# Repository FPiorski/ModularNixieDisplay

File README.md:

# Modular PCB for Z5730M Nixie tubes
#### Because ten small boards are better than a single big one
Schematics and board desing done in KiCad
##### ~~TODO for Rev 2:~~
* ~~Fix Z5730M footprint~~
  * ~~Widen mounting holes to account for desoldered tubes~~
  * ~~Bring mounting holes closer to center~~
* ~~Fix transistor pinout~~
  * ~~Change from Q_NPN_CBE to Q_NPN_BEC on the schematic~~
* ~~Reannotate components on the schematic~~
  * ~~Make R_n connect to Q_n and drive digit n~~
* ~~Add Rev 2 markings, of course~~

##### Revision 2 done!

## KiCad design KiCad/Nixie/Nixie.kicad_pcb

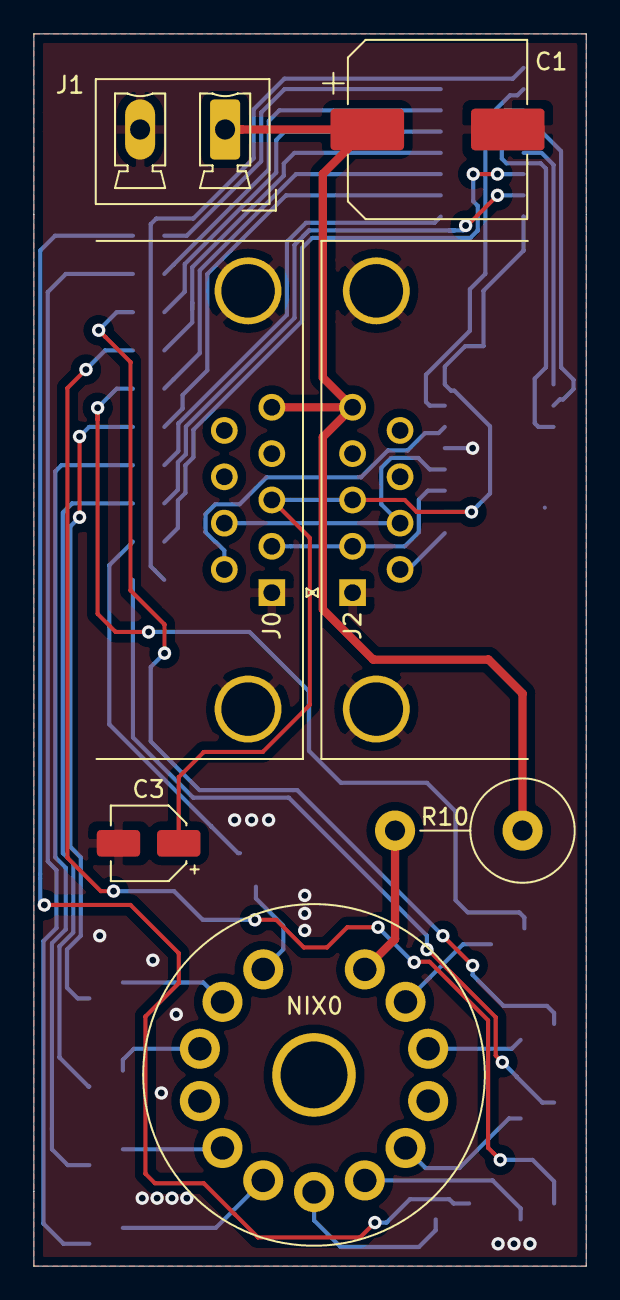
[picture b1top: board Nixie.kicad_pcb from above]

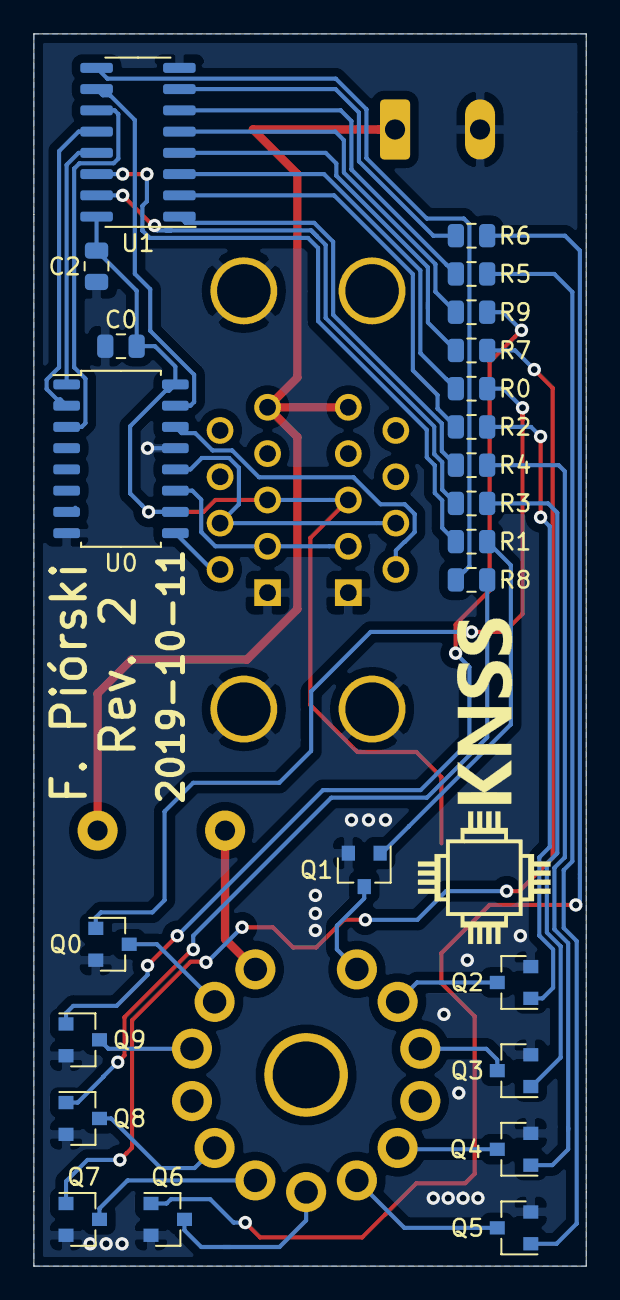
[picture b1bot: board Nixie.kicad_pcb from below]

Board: 2 copper layers, 33.0 x 73.7 mm, 31 parts (24 on the bottom side), 42 nets.

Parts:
C0, C2: 100n; C_0805_2012Metric
C1: 10u; CP_Elec_10x12.5
C3: 10u; CP_Elec_4x5.4
J0: DB9_Male_MountingHoles; DSUB-9_Female_Horizontal_P2.77x2.84mm_EdgePinOffset7.70mm_H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
J1: Screw_Terminal_01x02; PhoenixContact_MCV_1,5_2-G-5.08_1x02_P5.08mm_Vertical
J2: DB9_Female_MountingHoles; DSUB-9_Male_Horizontal_P2.77x2.84mm_EdgePinOffset7.70mm_Hou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
NIX0: NixieTube; Z5730M
Q0, Q1, Q2, Q3, Q4, Q5, Q6, Q7, Q8, Q9: Q_NPN_BEC; SOT-23
R0, R1, R2, R3, R4, R5, R6, R7, R8, R9: 47k; R_0805_2012Metric
R10: 15k; R_Axial_DIN0617_L17.0mm_D6.0mm_P7.62mm_Vertical
U0: 74HC595; SOP-16_4.55x10.3mm_P1.27mm
U1: 4028; SOIC-16_3.9x9.9mm_P1.27mm

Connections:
+5V: C0.1, C2.1, C3.1, J0.3, J2.3, U0.10, U0.16, U1.16
+170V: C1.1, J0.5, J1.1, J2.5, R10.1
/CLK: J0.2, J2.2, U0.11
/DATA_IN: J0.6, U0.14
/DATA_OUT: J2.6, U0.9
/LATCH: J0.7, J2.7, U0.12
GND: C0.2, C1.2, C2.2, C3.2, J0.0, J0.1, J1.2, J2.0, J2.1, Q0.2, Q1.2, Q2.2, Q3.2, Q4.2, Q5.2, Q6.2, Q7.2, Q8.2, Q9.2, U0.8, U0.13, U1.8
unnamed: NIX0.1, Q0.3
unnamed: NIX0.2, Q1.3
unnamed: NIX0.3, Q2.3
unnamed: NIX0.4, Q3.3
unnamed: NIX0.5, Q4.3
unnamed: NIX0.6, Q5.3
unnamed: NIX0.7, Q6.3
unnamed: NIX0.8, Q7.3
unnamed: NIX0.9, Q8.3
unnamed: NIX0.10, Q9.3
unnamed: NIX0.11, R10.2
unnamed: Q0.1, R0.1
unnamed: Q1.1, R1.1
unnamed: Q2.1, R2.1
unnamed: Q3.1, R3.1
unnamed: Q4.1, R4.1
unnamed: Q5.1, R5.1
unnamed: Q6.1, R6.1
unnamed: Q7.1, R7.1
unnamed: Q8.1, R8.1
unnamed: Q9.1, R9.1
unnamed: R0.2, U1.3
unnamed: R1.2, U1.14
unnamed: R2.2, U1.2
unnamed: R3.2, U1.15
unnamed: R4.2, U1.1
unnamed: R5.2, U1.6
unnamed: R6.2, U1.7
unnamed: R7.2, U1.4
unnamed: R8.2, U1.9
unnamed: R9.2, U1.5
unnamed: U0.1, U1.13
unnamed: U0.2, U1.12
unnamed: U0.3, U1.11
unnamed: U0.15, U1.10

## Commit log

2019-07-28 Added .gitattributes
2019-07-29 First version of the schematic, to be changed later
2019-07-29 First PCB draft
2019-07-31 PCB routing part 1
2019-08-07 Finished the board
2019-09-20 Added ESP32 code
2019-10-10 Revision 2
2019-10-10 Update README.md
    grammar fix
2019-10-15 Finally added the BoM
2020-02-13 Minor Schematic Change
2020-02-13 further git-KiCad integration
2020-02-13 Added a pdf export of the schematic
